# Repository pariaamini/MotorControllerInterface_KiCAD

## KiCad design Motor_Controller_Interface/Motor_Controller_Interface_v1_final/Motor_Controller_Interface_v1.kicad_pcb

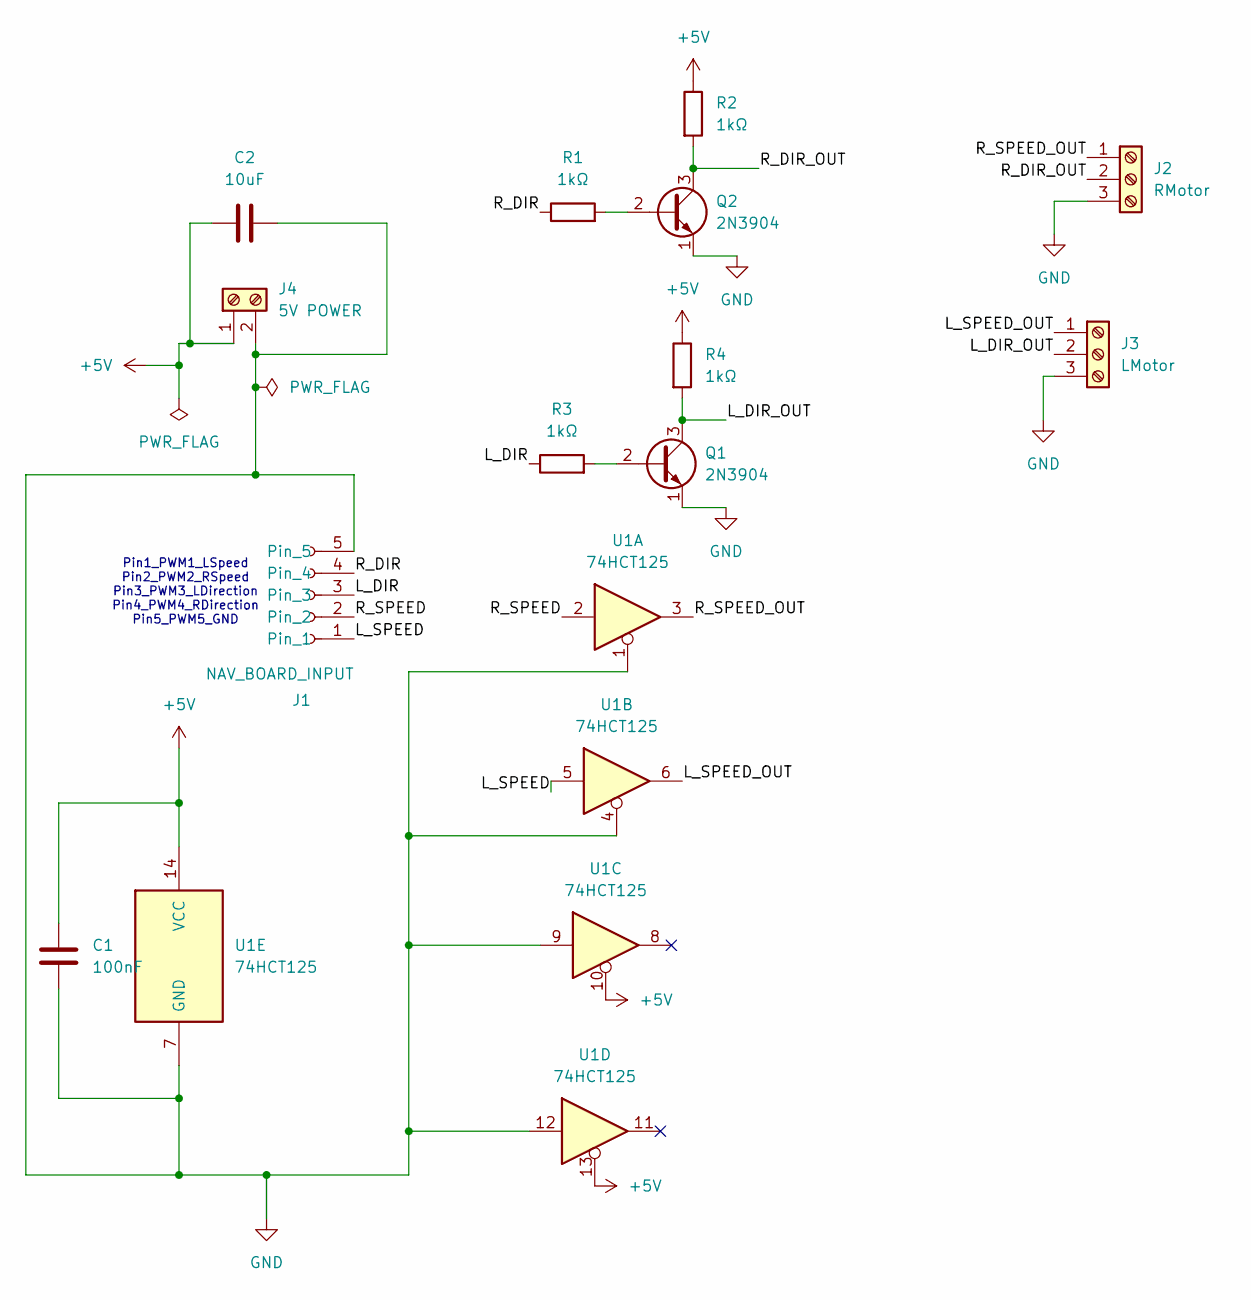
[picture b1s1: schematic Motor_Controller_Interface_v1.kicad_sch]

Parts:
C1: 100nF; C_0805_2012Metric_Pad1.18x1.45mm_HandSolder
C2: 10uF; C_1206_3216Metric_Pad1.33x1.80mm_HandSolder
J1: NAV_BOARD_INPUT; JST_GH_BM05B-GHS-TBT_1x05-1MP_P1.25mm_Vertical
J2: RMotor; TerminalBlock_4Ucon_1x03_P3.50mm_Horizontal
J3: LMotor; TerminalBlock_4Ucon_1x03_P3.50mm_Horizontal
J4: 5V POWER; TerminalBlock_4Ucon_1x02_P3.50mm_Horizontal
Q1, Q2: 2N3904; TO-92_Inline
R1, R2, R3, R4: 1kΩ; R_0805_2012Metric_Pad1.20x1.40mm_HandSolder
U1: 74HCT125; SOIC-14_3.9x8.7mm_P1.27mm

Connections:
+5V: C1.1, C2.1, J4.1, R2.1, R4.1, U1.10, U1.13, U1.14 (VCC)
/L_DIR: J1.3, R3.1
/L_DIR_OUT: J3.2, Q1.3 (C), R4.2
/L_SPEED: J1.1, U1.5
/L_SPEED_OUT: J3.1, U1.6
/R_DIR: J1.4, R1.1
/R_DIR_OUT: J2.2, Q2.3 (C), R2.2
/R_SPEED: J1.2, U1.2
/R_SPEED_OUT: J2.1, U1.3
GND: C1.2, C2.2, J1.5, J2.3, J3.3, J4.2, Q1.1 (E), Q2.1 (E), U1.1, U1.4, U1.7 (GND), U1.9, U1.12
unnamed: Q1.2 (B), R3.2
unnamed: Q2.2 (B), R1.2

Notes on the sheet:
Pin1_PWM1_LSpeed Pin2_PWM2_RSpeed Pin3_PWM3_LDirection Pin4_PWM4_RDirection Pin5_PWM5_GND

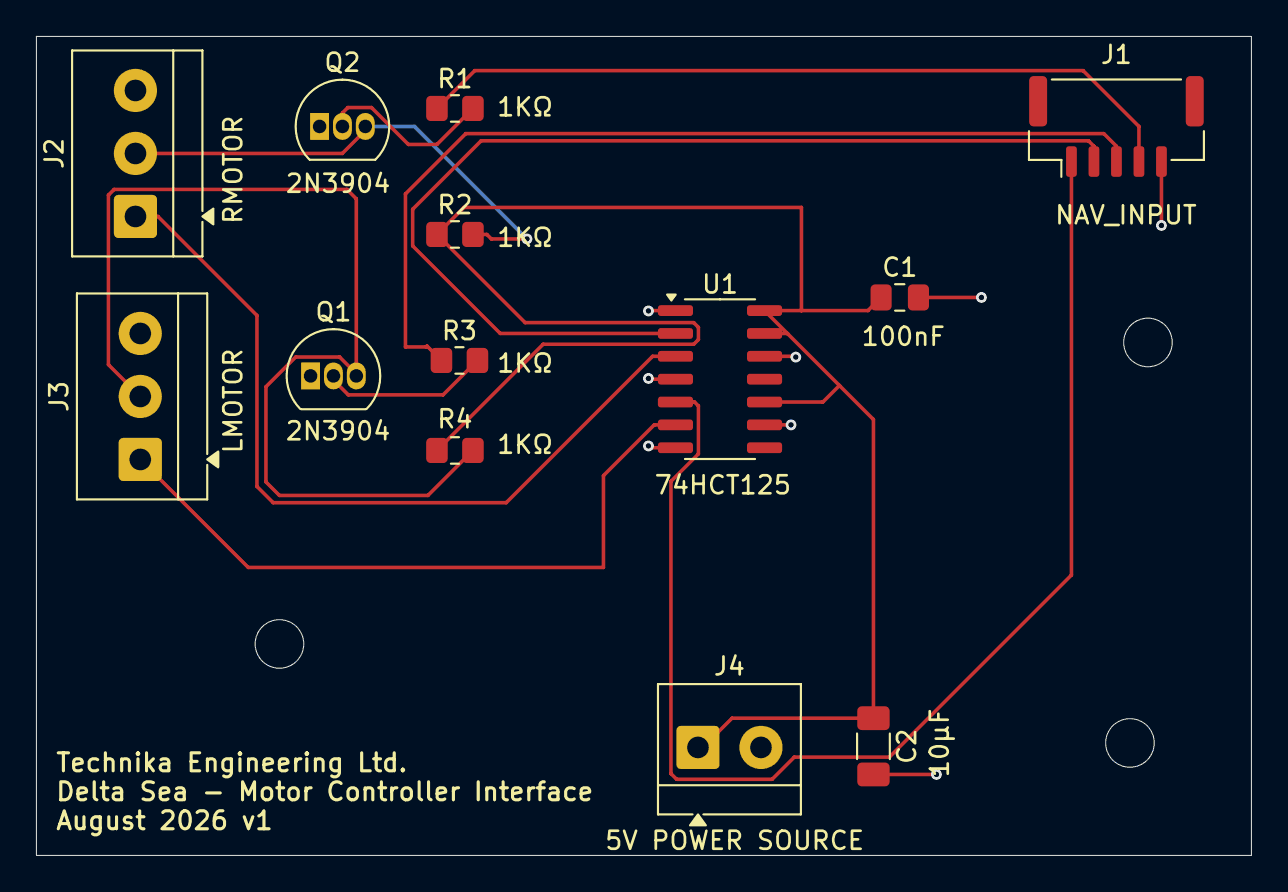
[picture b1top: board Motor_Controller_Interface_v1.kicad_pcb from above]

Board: 2 copper layers, 67.5 x 45.5 mm, 13 parts (0 on the bottom side), 12 nets.
